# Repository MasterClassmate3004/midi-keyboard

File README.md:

<h2>MIDI Keyboard</h2>

I created this MIDI Keyboard after inspiration from the HackClub Half Life challenge, midi keyboard guide for the Music themed week 3 project.

This includes 7 keys near the bottom left and 3 drum pads on the bottom right to play the songs you have always wanted to. 
It also includes 3 switches, one for going an octave higher, one for going an octave lower and the third one for sustaining the sound till held.
Lastly, it also includes 2 sliding potentiometers to adjust volume and modulation of the keyboard.

How this midi keyboard works is that whenever you press on the copper capacitive pads of the PCB the circuit is completed and our ESP32 S3 detects and sends commands
to the connected computer indicating what key is pressed. Then, accordingly the computer looks at the firmware and understands what sound to play because this key is 
pressed. This is basically how our keyboard works. Additional features go a bit more complex on how do they work but yeah this is the essential principle behind it.

For the drum pads, one is for kick, one is for snare and the last one is for hi-hat sound.

To build this project, order the pcb using the gerbers.zip file in the Production folder. Also order the required components for this as mentioned below:
<ul>
  <li> 1x Waveshare ESP32 S3</li>
  <li> 2x Bourns Sliding Potentiometer</li>
  <li> 3x Cherry MX Switches</li>
  <li> 3x Cherry MX Keycaps</li>
</ul>

This is all we need except the PCB for the project. Once you receive all the components and the pcb, solder them to their repsective positions. Then load the firmware
to the ESP32 S3 using the Arduino IDE. The firmware is present in the productions folder. To upload, select the required port and board in the Arduino IDE. You are free
to make changes to firmware to change any sounds or functions of the potentiometer or keys as you like. After uploading the firmware, keep the usb cable connected to the
computer and start pressing the keyboard keys and drumpads and experimenting this. Make your own songs and share them on  HackClub's Slack server.

<br>
<hr>
<br>

<h4>Schematics</h4>

<br>
<hr>
<br>

<h4>PCB Routing</h4>

<br>
<hr>
<br>

<h4>PCB Front View</h4>

<br>
<hr>
<br>

<h4>PCB Back View</h4>

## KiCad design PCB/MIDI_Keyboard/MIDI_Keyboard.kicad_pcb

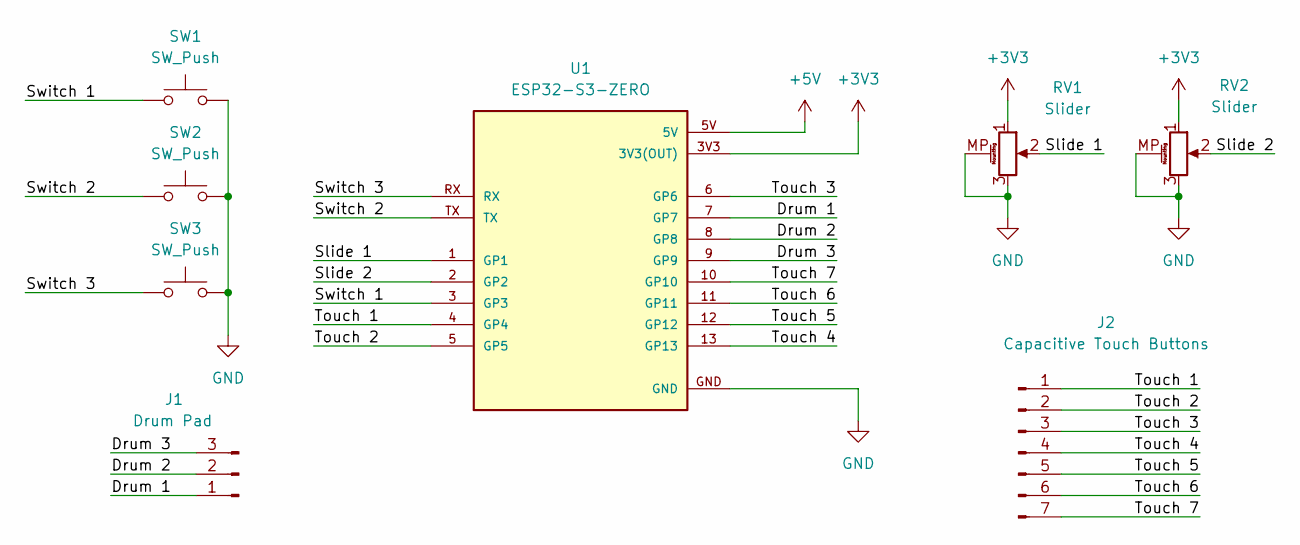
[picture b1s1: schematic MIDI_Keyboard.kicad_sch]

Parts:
J1: Drum Pad; DrumPad
J2: Capacitive Touch Buttons; MIDI_Keyboard
RV1, RV2: Slider; Potentiometer_Bourns_PTA1543_Single_Slide
SW1, SW2, SW3: SW_Push; SW_Cherry_MX_1.00u_PCB
U1: ESP32-S3-ZERO; MODULE_ESP32-S3-ZERO; PARTREV NA

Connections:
+3V3: RV1.1, RV2.1, U1.3V3 (3V3(OUT))
+5V: U1.5V
/Drum 1: J1.1, U1.7 (GP7)
/Drum 2: J1.2, U1.8 (GP8)
/Drum 3: J1.3, U1.9 (GP9)
/Slide 1: RV1.2, U1.1 (GP1)
/Slide 2: RV2.2, U1.2 (GP2)
/Switch 1: SW1.1, U1.3 (GP3)
/Switch 2: SW2.1, U1.TX
/Switch 3: SW3.1, U1.RX
/Touch 1: J2.1, U1.4 (GP4)
/Touch 2: J2.2, U1.5 (GP5)
/Touch 3: J2.3, U1.6 (GP6)
/Touch 4: J2.4, U1.13 (GP13)
/Touch 5: J2.5, U1.12 (GP12)
/Touch 6: J2.6, U1.11 (GP11)
/Touch 7: J2.7, U1.10 (GP10)
GND: RV1.3, RV1.MP (MountPin), RV2.3, RV2.MP (MountPin), SW1.2, SW2.2, SW3.2, U1.GND

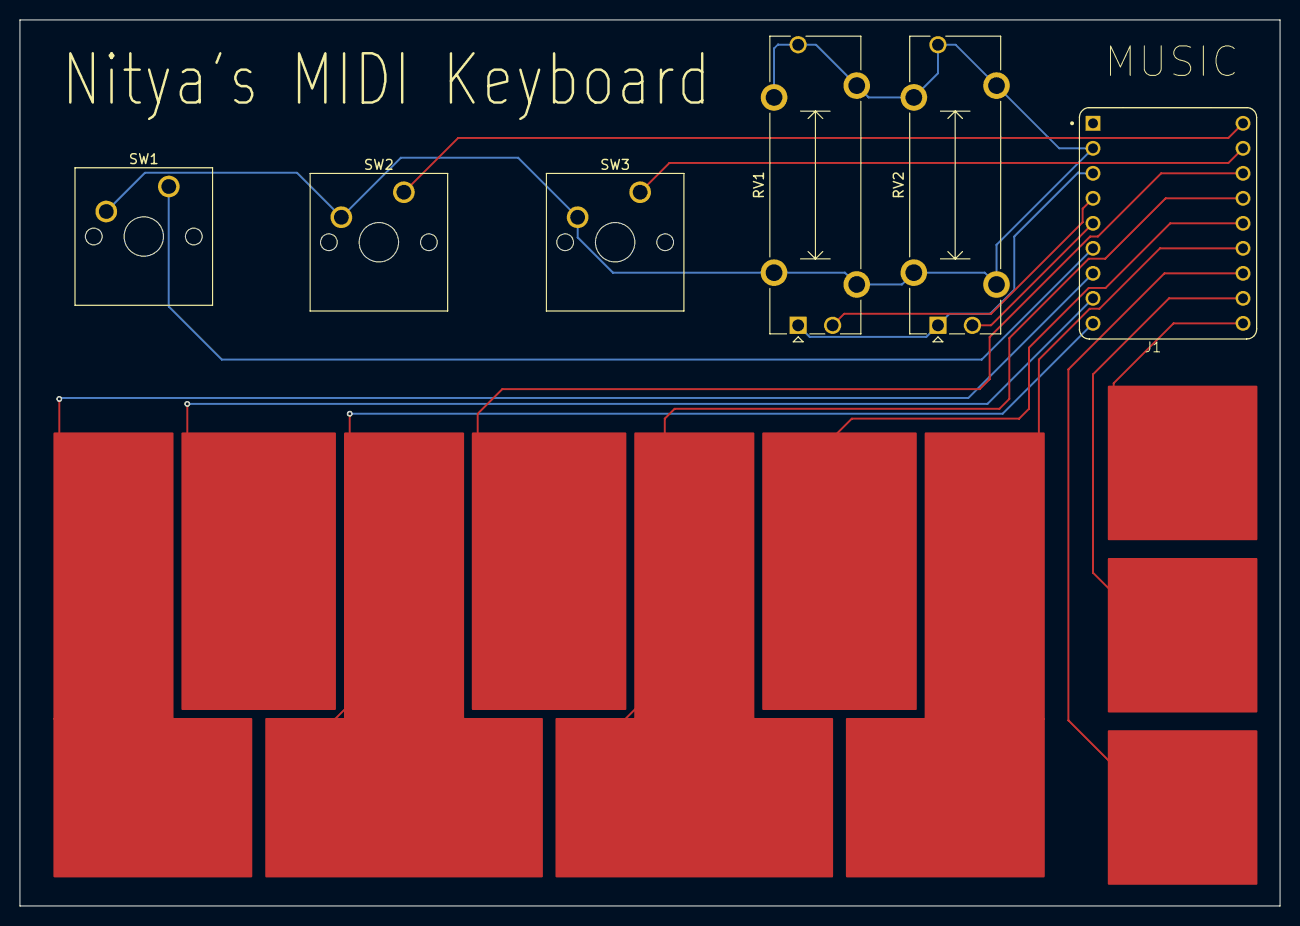
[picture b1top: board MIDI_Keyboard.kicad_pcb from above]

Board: 2 copper layers, 128.0 x 90.0 mm, 8 parts (0 on the bottom side), 17 nets.
